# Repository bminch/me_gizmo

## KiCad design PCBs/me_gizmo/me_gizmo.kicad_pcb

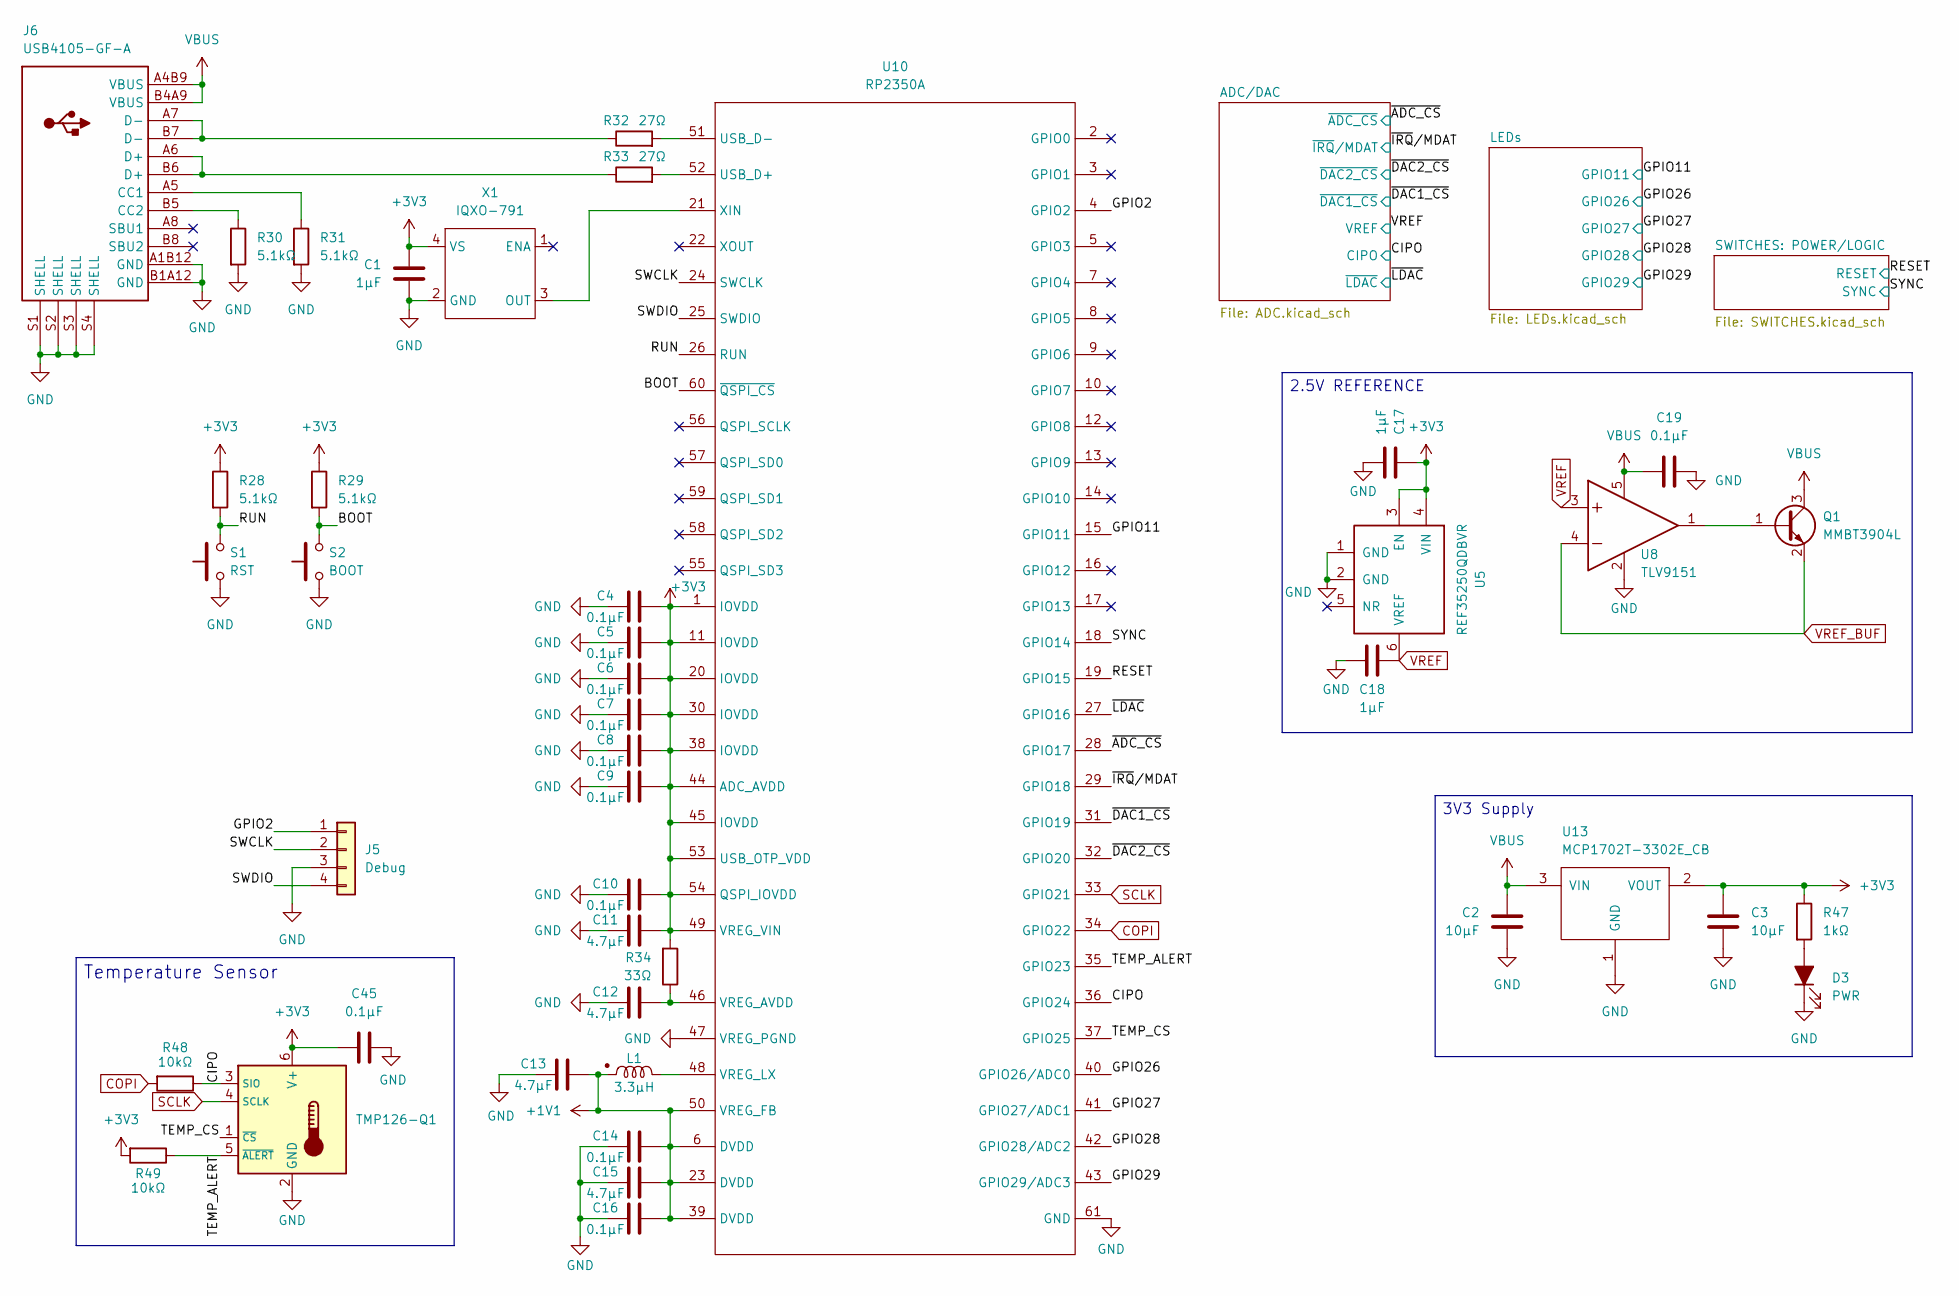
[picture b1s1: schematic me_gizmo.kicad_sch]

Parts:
C1: 1µF; C_0402_1005Metric
C2, C3: 10µF; C_0603_1608Metric
C4, C5, C6, C7, C8, C9, C10, C14, C16: 0.1µF; C_0402_1005Metric
C11, C12, C13, C15: 4.7µF; C_0402_1005Metric
C17, C18: 1µF; C_0603_1608Metric
C19, C45: 0.1µF; C_0603_1608Metric
D3: PWR; LED_0805_2012Metric
J5: Debug; PinHeader_1x04_P2.54mm_Vertical
J6: USB4105-GF-A
L1: 3.3µH; AOTA-B201610S3R3-101-T
Q1: MMBT3904L; SOT-23
R28, R29, R30, R31: 5.1kΩ; R_0603_1608Metric
R32, R33: 27Ω; R_0402_1005Metric
R34: 33Ω; R_0402_1005Metric
R47: 1kΩ; R_0603_1608Metric
R48, R49: 10kΩ; R_0603_1608Metric
S1: RST; SW_SPST_B3U-1000P
S2: BOOT; SW_SPST_B3U-1000P
U5: REF35250QDBVR; SOT-23-6
U6: TMP126-Q1; SOT-23-6
U8: TLV9151; SOT-23-5
U10: RP2350A; RP2350A_QFN-60_EP_7.75x7.75_Pitch0.4mm
U13: MCP1702T-3302E_CB; SOT-23
X1: IQXO-791

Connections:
+1V1: C13.2, C14.2, C15.2, C16.2, L1.1, U10.6 (DVDD), U10.23 (DVDD), U10.39 (DVDD), U10.50 (VREG_FB)
+3V3: C1.2, C3.1, C4.2, C5.2, C6.2, C7.2, C8.2, C9.2, C10.2, C11.2, C17.1, C45.1, R28.1, R29.1, R34.2, R47.1, R49.2, U5.3 (EN), U5.4 (VIN), U6.6 (V+), U10.1 (IOVDD), U10.11 (IOVDD), U10.20 (IOVDD), U10.30 (IOVDD), U10.38 (IOVDD), U10.44 (ADC_AVDD), U10.45 (IOVDD), U10.49 (VREG_VIN), U10.53 (USB_OTP_VDD), U10.54 (QSPI_IOVDD), U13.2 (VOUT), X1.4 (VS); also elsewhere on the board
/BOOT: R29.2, S2.2, U10.60 (~QSPI_CS)
/CIPO: R48.1, U6.3 (SIO), U10.36 (GPIO24); also elsewhere on the board
/GPIO2: J5.1, U10.4 (GPIO2)
/GPIO11: U10.15 (GPIO11); also elsewhere on the board
/GPIO26: U10.40 (GPIO26/ADC0); also elsewhere on the board
/GPIO27: U10.41 (GPIO27/ADC1); also elsewhere on the board
/GPIO28: U10.42 (GPIO28/ADC2); also elsewhere on the board
/GPIO29: U10.43 (GPIO29/ADC3); also elsewhere on the board
/RESET: U10.19 (GPIO15); also elsewhere on the board
/RUN: R28.2, S1.2, U10.26 (RUN)
/SWCLK: J5.2, U10.24 (SWCLK)
/SWDIO: J5.4, U10.25 (SWDIO)
/SYNC: U10.18 (GPIO14); also elsewhere on the board
/TEMP_ALERT: R49.1, U6.5 (~ALERT), U10.35 (GPIO23)
/TEMP_CS: U6.1 (~CS), U10.37 (GPIO25)
/~ADC_CS: U10.28 (GPIO17); also elsewhere on the board
/~DAC1_CS: U10.31 (GPIO19); also elsewhere on the board
/~DAC2_CS: U10.32 (GPIO20); also elsewhere on the board
/~IRQ/MDAT: U10.29 (GPIO18); also elsewhere on the board
/~LDAC: U10.27 (GPIO16); also elsewhere on the board
COPI: R48.2, U10.34 (GPIO22); also elsewhere on the board
GND: C1.1, C2.1, C3.2, C4.1, C5.1, C6.1, C7.1, C8.1, C9.1, C10.1, C11.1, C12.1, C13.1, C14.1, C15.1, C16.1, C17.2, C18.2, C19.2, C45.2, D3.1 (K), J5.3, J6.A1B12 (GND), J6.B1A12 (GND), J6.S1 (SHELL), J6.S2 (SHELL), J6.S3 (SHELL), J6.S4 (SHELL), R30.2, R31.2, S1.1, S2.1, U5.1 (GND), U5.2 (GND), U6.2 (GND), U8.2, U10.47 (VREG_PGND), U10.61 (GND), U13.1 (GND), X1.2 (GND); also elsewhere on the board
unnamed: D3.2 (A), R47.2
unnamed: J6.A5 (CC1), R31.1
unnamed: J6.B5 (CC2), R30.1
unnamed: J6.A6 (D+), J6.B6 (D+), R33.1
unnamed: J6.A7 (D-), J6.B7 (D-), R32.1
unnamed: Q1.1 (B), U8.1
unnamed: R33.2, U10.52 (USB_D+)
unnamed: R32.2, U10.51 (USB_D-)
unnamed: C12.2, R34.1, U10.46 (VREG_AVDD)
unnamed: L1.2, U10.48 (VREG_LX)
unnamed: U10.21 (XIN), X1.3 (OUT)
SCLK: U6.4 (SCLK), U10.33 (GPIO21); also elsewhere on the board
VBUS: C2.2, C19.1, J6.A4B9 (VBUS), J6.B4A9 (VBUS), Q1.3 (C), U8.5, U13.3 (VIN)
VREF: C18.1, U5.6 (VREF), U8.3; also elsewhere on the board
VREF_BUF: Q1.2 (E), U8.4; also elsewhere on the board

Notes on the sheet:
2.5V REFERENCE
Temperature Sensor
3V3 Supply

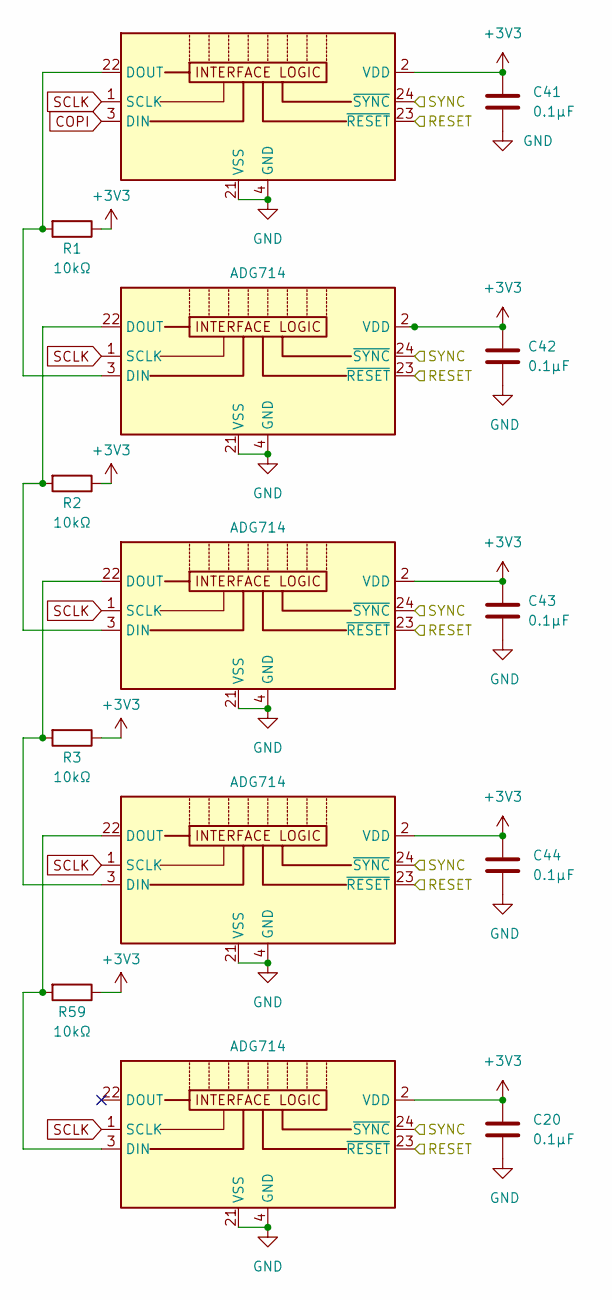
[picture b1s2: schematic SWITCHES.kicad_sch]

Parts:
C20, C41, C42, C43, C44: 0.1µF; C_0603_1608Metric
R1, R2, R3, R59: 10kΩ; R_0603_1608Metric
U1, U2, U3, U4, U7: ADG714; TSSOP-24_4.4x7.8mm_P0.65mm

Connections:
+3V3: C20.1, C41.1, C42.1, C43.1, C44.1, R1.1, R2.1, R3.1, R59.1, U1.2 (VDD), U2.2 (VDD), U3.2 (VDD), U4.2 (VDD), U7.2 (VDD); also elsewhere on the board
/RESET: U1.23 (~RESET), U2.23 (~RESET), U3.23 (~RESET), U4.23 (~RESET), U7.23 (~RESET); also elsewhere on the board
/SYNC: U1.24 (~SYNC), U2.24 (~SYNC), U3.24 (~SYNC), U4.24 (~SYNC), U7.24 (~SYNC); also elsewhere on the board
COPI: U7.3 (DIN); also elsewhere on the board
GND: C20.2, C41.2, C42.2, C43.2, C44.2, U1.4 (GND), U1.21 (VSS), U2.4 (GND), U2.21 (VSS), U3.4 (GND), U3.21 (VSS), U4.4 (GND), U4.21 (VSS), U7.4 (GND), U7.21 (VSS); also elsewhere on the board
unnamed: R1.2, U1.3 (DIN), U7.22 (DOUT)
unnamed: R2.2, U1.22 (DOUT), U4.3 (DIN)
unnamed: R59.2, U2.3 (DIN), U3.22 (DOUT)
unnamed: R3.2, U3.3 (DIN), U4.22 (DOUT)
SCLK: U1.1 (SCLK), U2.1 (SCLK), U3.1 (SCLK), U4.1 (SCLK), U7.1 (SCLK); also elsewhere on the board

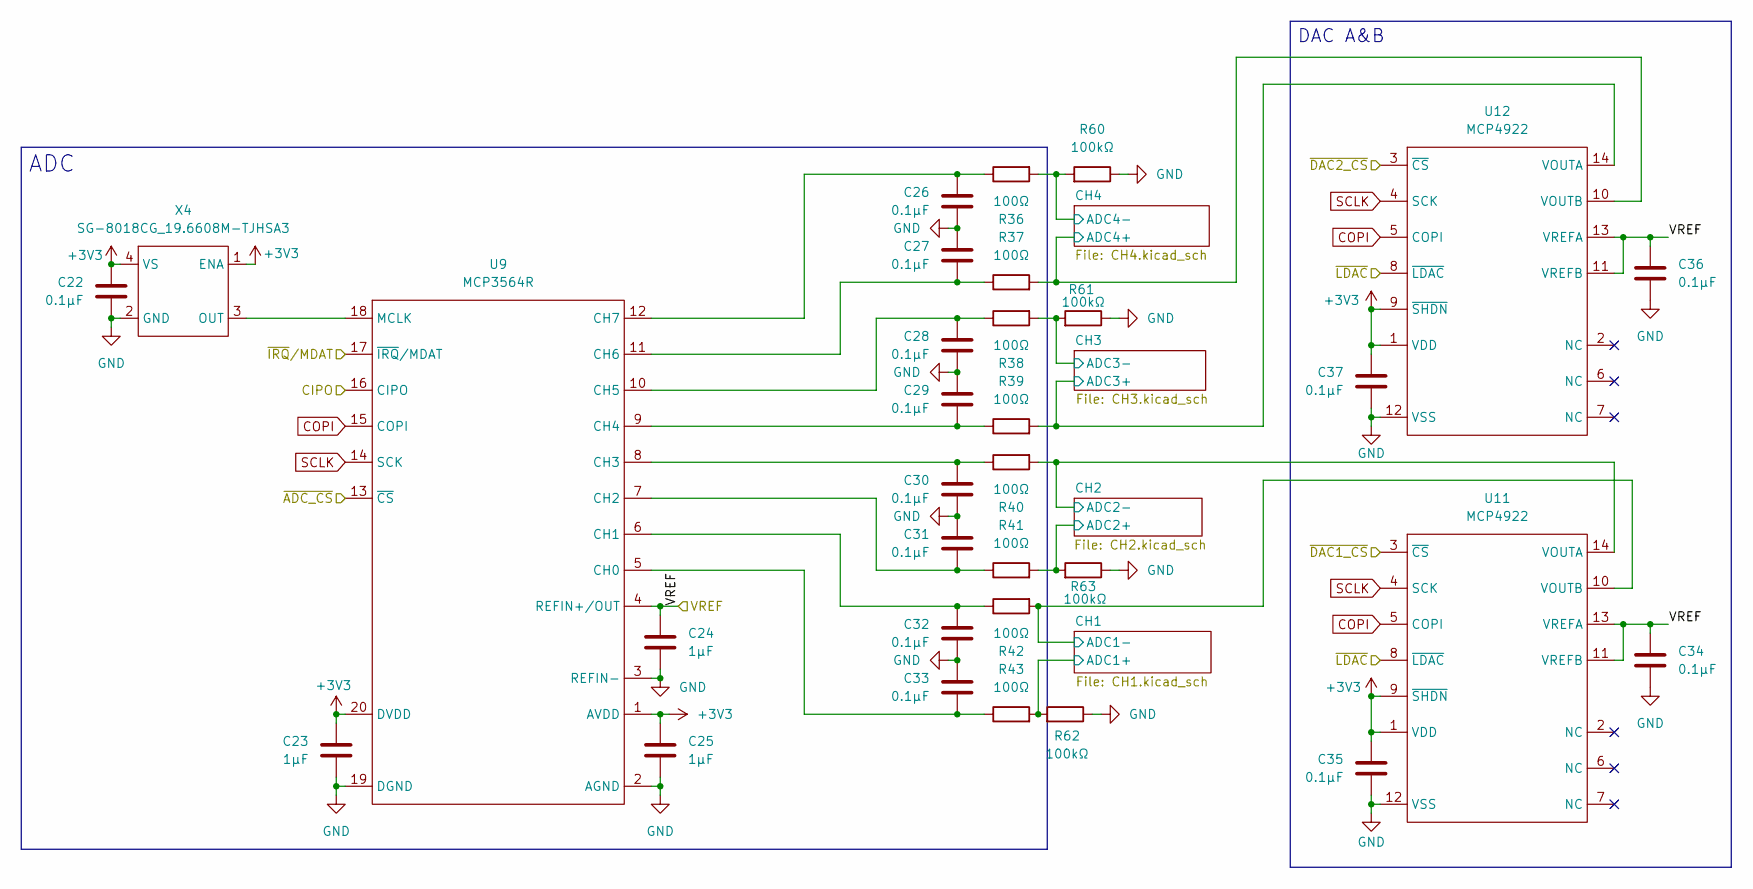
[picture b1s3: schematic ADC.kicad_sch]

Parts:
C22, C26, C27, C28, C29, C30, C31, C32, C33, C34, C35, C36, C37: 0.1µF; C_0603_1608Metric
C23, C24, C25: 1µF; C_0603_1608Metric
R36, R37, R38, R39, R40, R41, R42, R43: 100Ω; R_0603_1608Metric
R60, R61, R62, R63: 100kΩ; R_0603_1608Metric
U9: MCP3564R; TSSOP-20_4.4x6.5mm_P0.65mm
U11, U12: MCP4922; TSSOP-14_4.4x5mm_P0.65mm
X4: SG-8018CG_19.6608M-TJHSA3; Crystal_SMD_2520-4Pin_2.5x2.0mm

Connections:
+3V3: C22.1, C23.1, C25.1, C35.1, C37.1, U9.1 (AVDD), U9.20 (DVDD), U11.1 (VDD), U11.9 (~SHDN), U12.1 (VDD), U12.9 (~SHDN), X4.1 (ENA), X4.4 (VS); also elsewhere on the board
/ADC/DAC/CH1/ADC1+: R43.2, R62.2; also elsewhere on the board
/ADC/DAC/CH1/ADC1-: R42.2, U11.10 (VOUTB); also elsewhere on the board
/ADC/DAC/CH2/ADC2+: R41.2, R63.2; also elsewhere on the board
/ADC/DAC/CH2/ADC2-: R40.2, U11.14 (VOUTA); also elsewhere on the board
/ADC/DAC/CH3/ADC3+: R39.2, U12.14 (VOUTA); also elsewhere on the board
/ADC/DAC/CH3/ADC3-: R38.2, R61.2; also elsewhere on the board
/ADC/DAC/CH4/ADC4+: R37.2, U12.10 (VOUTB); also elsewhere on the board
/ADC/DAC/CH4/ADC4-: R36.2, R60.2; also elsewhere on the board
/CIPO: U9.16 (CIPO); also elsewhere on the board
/~ADC_CS: U9.13 (~CS); also elsewhere on the board
/~DAC1_CS: U11.3 (~CS); also elsewhere on the board
/~DAC2_CS: U12.3 (~CS); also elsewhere on the board
/~IRQ/MDAT: U9.17 (~IRQ/MDAT); also elsewhere on the board
/~LDAC: U11.8 (~LDAC), U12.8 (~LDAC); also elsewhere on the board
COPI: U9.15 (COPI), U11.5 (COPI), U12.5 (COPI); also elsewhere on the board
GND: C22.2, C23.2, C24.2, C25.2, C26.2, C27.1, C28.2, C29.1, C30.2, C31.1, C32.2, C33.1, C34.2, C35.2, C36.2, C37.2, R60.1, R61.1, R62.1, R63.1, U9.2 (AGND), U9.3 (REFIN-), U9.19 (DGND), U11.12 (VSS), U12.12 (VSS), X4.2 (GND); also elsewhere on the board
unnamed: C33.2, R43.1, U9.5 (CH0)
unnamed: C32.1, R42.1, U9.6 (CH1)
unnamed: C31.2, R41.1, U9.7 (CH2)
unnamed: C30.1, R40.1, U9.8 (CH3)
unnamed: C29.2, R39.1, U9.9 (CH4)
unnamed: C28.1, R38.1, U9.10 (CH5)
unnamed: C27.2, R37.1, U9.11 (CH6)
unnamed: C26.1, R36.1, U9.12 (CH7)
unnamed: U9.18 (MCLK), X4.3 (OUT)
SCLK: U9.14 (SCK), U11.4 (SCK), U12.4 (SCK); also elsewhere on the board
VREF: C24.1, C34.1, C36.1, U9.4 (REFIN+/OUT), U11.11 (VREFB), U11.13 (VREFA), U12.11 (VREFB), U12.13 (VREFA); also elsewhere on the board

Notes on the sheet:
DAC A&B
ADC

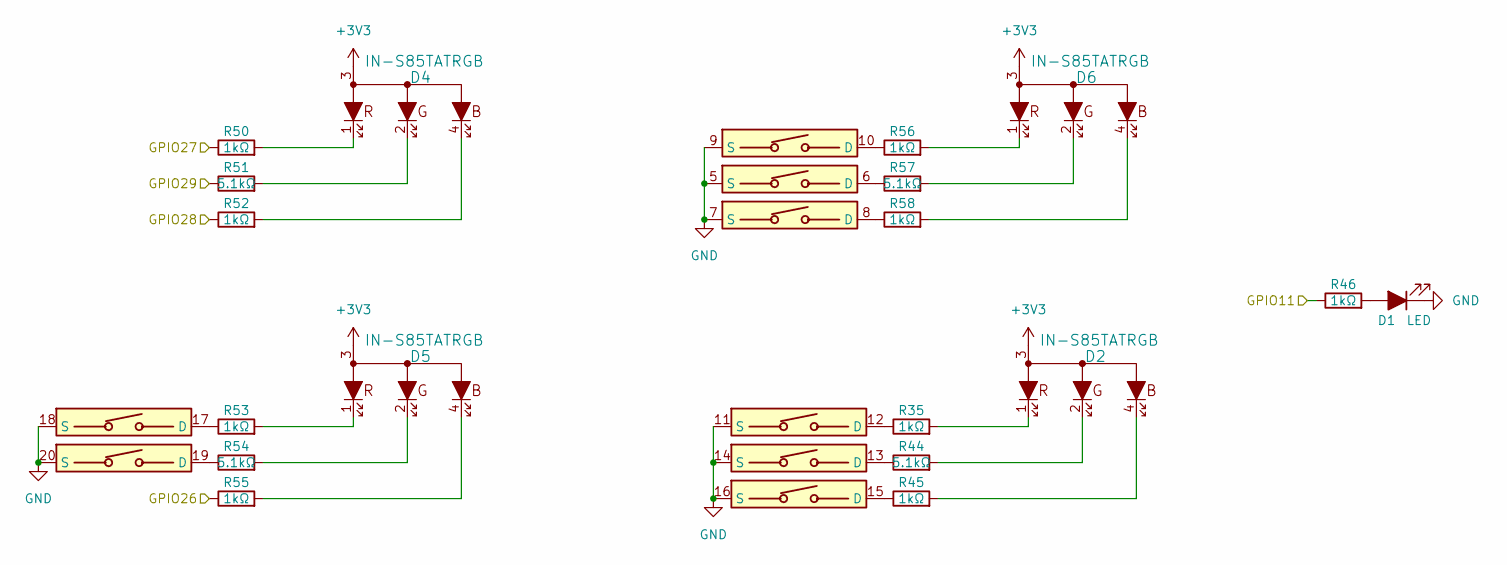
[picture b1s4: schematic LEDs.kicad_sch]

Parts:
D1: LED; LED_0805_2012Metric
D2, D4, D5, D6: IN-S85TATRGB
R35, R45, R46, R50, R52, R53, R55, R56, R58: 1kΩ; R_0603_1608Metric
R44, R51, R54, R57: 5.1kΩ; R_0603_1608Metric
U7: ADG714; TSSOP-24_4.4x7.8mm_P0.65mm

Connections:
+3V3: D2.3, D4.3, D5.3, D6.3; also elsewhere on the board
/GPIO11: R46.1; also elsewhere on the board
/GPIO26: R55.1; also elsewhere on the board
/GPIO27: R50.1; also elsewhere on the board
/GPIO28: R52.1; also elsewhere on the board
/GPIO29: R51.1; also elsewhere on the board
GND: D1.1 (K), U7.5 (S), U7.7 (S), U7.9 (S), U7.11 (S), U7.14 (S), U7.16 (S), U7.18 (S), U7.20 (S); also elsewhere on the board
unnamed: D1.2 (A), R46.2
unnamed: D2.1, R35.2
unnamed: D2.2, R44.2
unnamed: D2.4, R45.2
unnamed: D4.1, R50.2
unnamed: D4.2, R51.2
unnamed: D4.4, R52.2
unnamed: D5.1, R53.2
unnamed: D5.2, R54.2
unnamed: D5.4, R55.2
unnamed: D6.1, R56.2
unnamed: D6.2, R57.2
unnamed: D6.4, R58.2
unnamed: R57.1, U7.6 (D)
unnamed: R58.1, U7.8 (D)
unnamed: R56.1, U7.10 (D)
unnamed: R35.1, U7.12 (D)
unnamed: R44.1, U7.13 (D)
unnamed: R45.1, U7.15 (D)
unnamed: R53.1, U7.17 (D)
unnamed: R54.1, U7.19 (D)

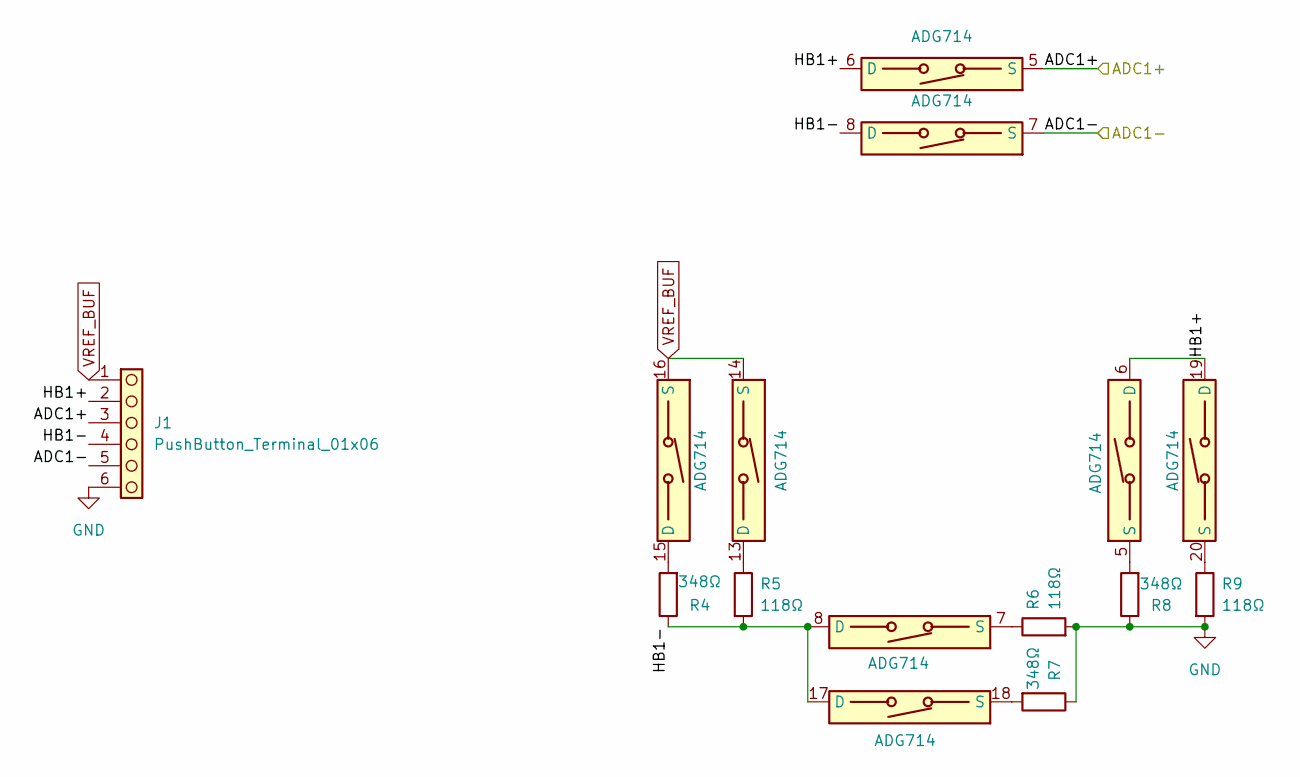
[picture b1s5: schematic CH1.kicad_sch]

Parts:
J1: PushButton_Terminal_01x06; TerminalBlock_WAGO_233-506_2x06_P2.54mm
R4, R7, R8: 348Ω; R_0603_1608Metric
R5, R6, R9: 118Ω; R_0603_1608Metric
U1, U2, U3: ADG714; TSSOP-24_4.4x7.8mm_P0.65mm

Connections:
/ADC/DAC/CH1/ADC1+: J1.3, U3.5 (S); also elsewhere on the board
/ADC/DAC/CH1/ADC1-: J1.5, U3.7 (S); also elsewhere on the board
/ADC/DAC/CH1/HB1+: J1.2, U2.6 (D), U2.19 (D), U3.6 (D)
/ADC/DAC/CH1/HB1-: J1.4, R4.1, R5.2, U2.8 (D), U2.17 (D), U3.8 (D)
GND: J1.6, R6.2, R7.1, R8.1, R9.2; also elsewhere on the board
unnamed: R5.1, U1.13 (D)
unnamed: R4.2, U1.15 (D)
unnamed: R8.2, U2.5 (S)
unnamed: R6.1, U2.7 (S)
unnamed: R7.2, U2.18 (S)
unnamed: R9.1, U2.20 (S)
VREF_BUF: J1.1, U1.14 (S), U1.16 (S); also elsewhere on the board

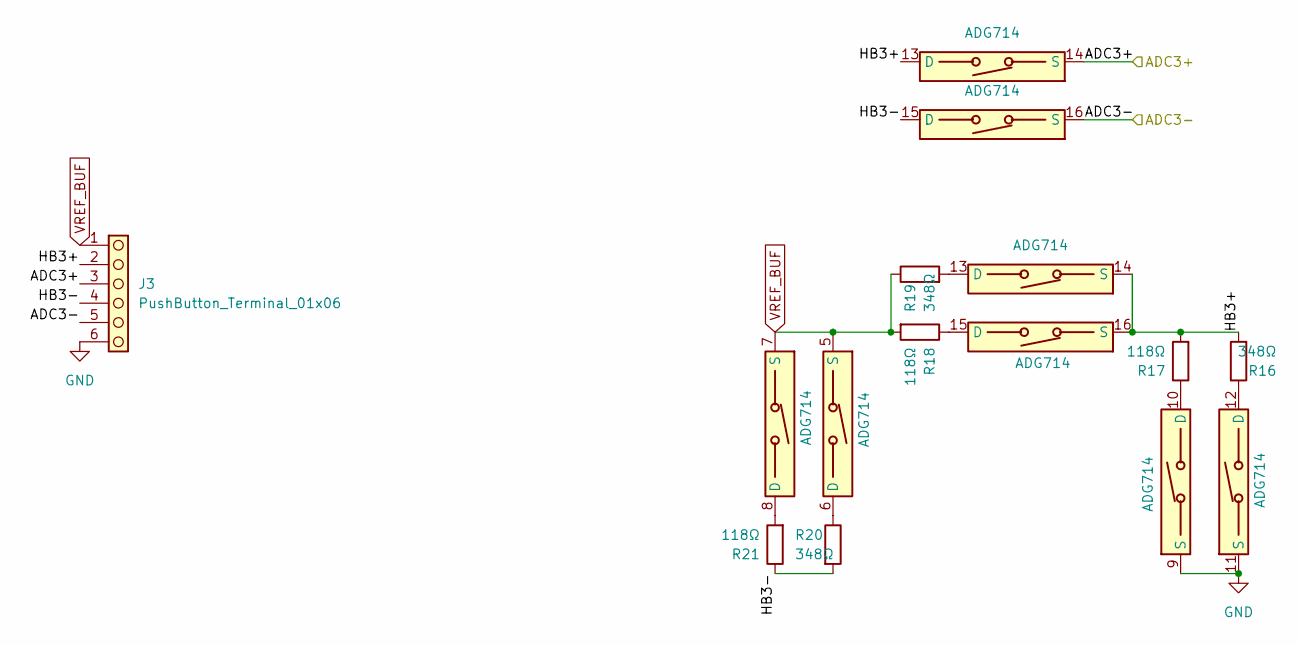
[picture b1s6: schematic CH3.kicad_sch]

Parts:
J3: PushButton_Terminal_01x06; TerminalBlock_WAGO_233-506_2x06_P2.54mm
R16, R19, R20: 348Ω; R_0603_1608Metric
R17, R18, R21: 118Ω; R_0603_1608Metric
U1, U3, U4: ADG714; TSSOP-24_4.4x7.8mm_P0.65mm

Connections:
/ADC/DAC/CH3/ADC3+: J3.3, U3.14 (S); also elsewhere on the board
/ADC/DAC/CH3/ADC3-: J3.5, U3.16 (S); also elsewhere on the board
/ADC/DAC/CH3/HB3+: J3.2, R16.2, R17.2, U3.13 (D), U4.14 (S), U4.16 (S)
/ADC/DAC/CH3/HB3-: J3.4, R20.2, R21.1, U3.15 (D)
GND: J3.6, U4.9 (S), U4.11 (S); also elsewhere on the board
unnamed: R20.1, U1.6 (D)
unnamed: R21.2, U1.8 (D)
unnamed: R17.1, U4.10 (D)
unnamed: R16.1, U4.12 (D)
unnamed: R19.2, U4.13 (D)
unnamed: R18.1, U4.15 (D)
VREF_BUF: J3.1, R18.2, R19.1, U1.5 (S), U1.7 (S); also elsewhere on the board

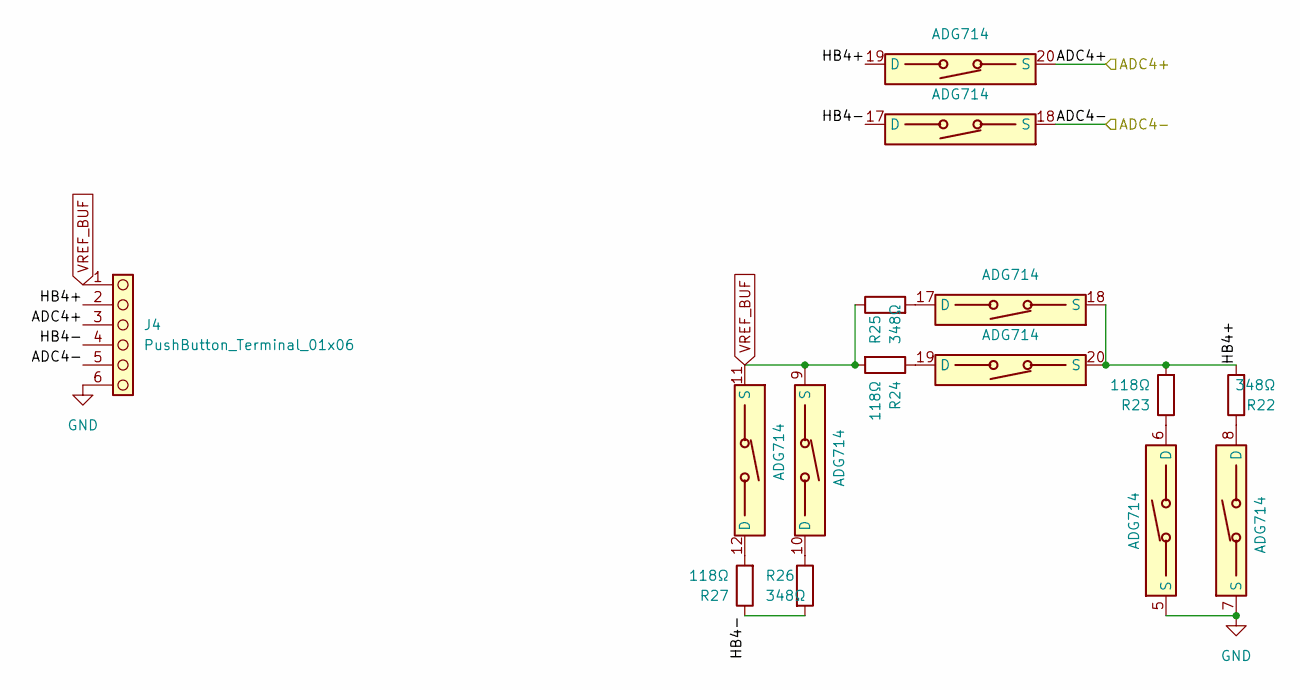
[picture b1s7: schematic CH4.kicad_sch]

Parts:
J4: PushButton_Terminal_01x06; TerminalBlock_WAGO_233-506_2x06_P2.54mm
R22, R25, R26: 348Ω; R_0603_1608Metric
R23, R24, R27: 118Ω; R_0603_1608Metric
U1, U3, U4: ADG714; TSSOP-24_4.4x7.8mm_P0.65mm

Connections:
/ADC/DAC/CH4/ADC4+: J4.3, U3.20 (S); also elsewhere on the board
/ADC/DAC/CH4/ADC4-: J4.5, U3.18 (S); also elsewhere on the board
/ADC/DAC/CH4/HB4+: J4.2, R22.2, R23.2, U3.19 (D), U4.18 (S), U4.20 (S)
/ADC/DAC/CH4/HB4-: J4.4, R26.2, R27.1, U3.17 (D)
GND: J4.6, U4.5 (S), U4.7 (S); also elsewhere on the board
unnamed: R26.1, U1.10 (D)
unnamed: R27.2, U1.12 (D)
unnamed: R23.1, U4.6 (D)
unnamed: R22.1, U4.8 (D)
unnamed: R25.2, U4.17 (D)
unnamed: R24.1, U4.19 (D)
VREF_BUF: J4.1, R24.2, R25.1, U1.9 (S), U1.11 (S); also elsewhere on the board

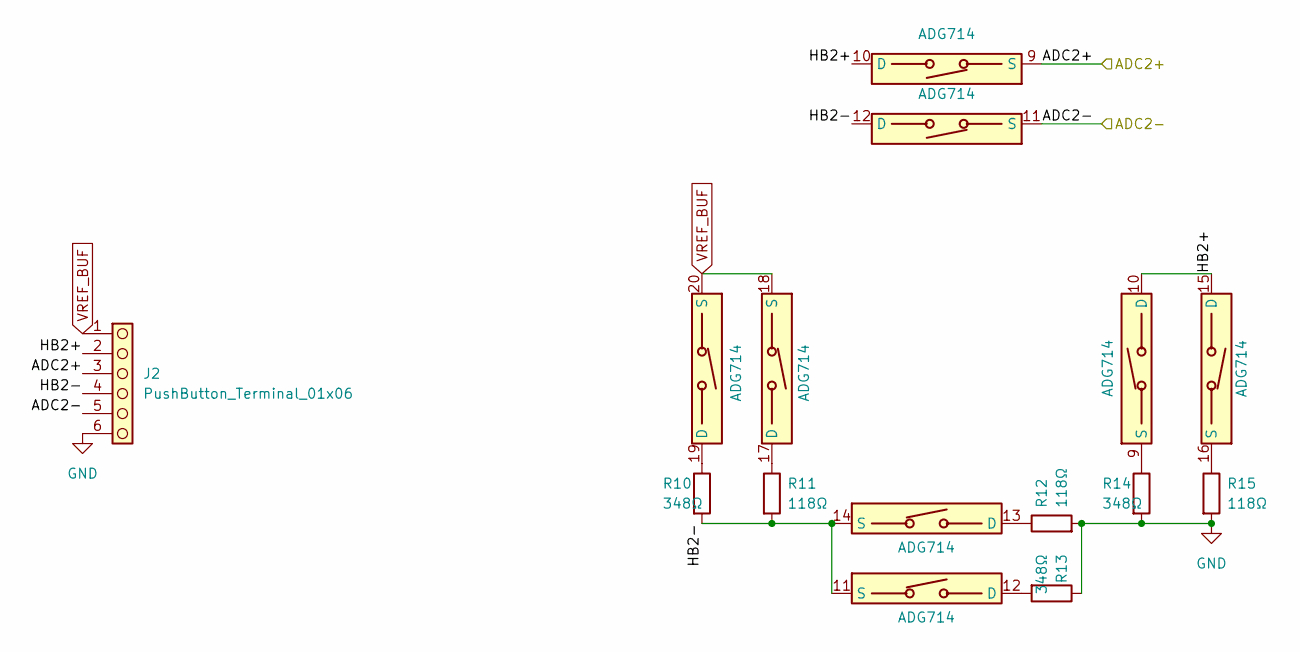
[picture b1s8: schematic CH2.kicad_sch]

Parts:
J2: PushButton_Terminal_01x06; TerminalBlock_WAGO_233-506_2x06_P2.54mm
R10, R13, R14: 348Ω; R_0603_1608Metric
R11, R12, R15: 118Ω; R_0603_1608Metric
U1, U2, U3: ADG714; TSSOP-24_4.4x7.8mm_P0.65mm

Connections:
/ADC/DAC/CH2/ADC2+: J2.3, U3.9 (S); also elsewhere on the board
/ADC/DAC/CH2/ADC2-: J2.5, U3.11 (S); also elsewhere on the board
/ADC/DAC/CH2/HB2+: J2.2, U2.10 (D), U2.15 (D), U3.10 (D)
/ADC/DAC/CH2/HB2-: J2.4, R10.2, R11.2, U2.11 (S), U2.14 (S), U3.12 (D)
GND: J2.6, R12.2, R13.1, R14.2, R15.2; also elsewhere on the board
unnamed: R11.1, U1.17 (D)
unnamed: R10.1, U1.19 (D)
unnamed: R14.1, U2.9 (S)
unnamed: R13.2, U2.12 (D)
unnamed: R12.1, U2.13 (D)
unnamed: R15.1, U2.16 (S)
VREF_BUF: J2.1, U1.18 (S), U1.20 (S); also elsewhere on the board

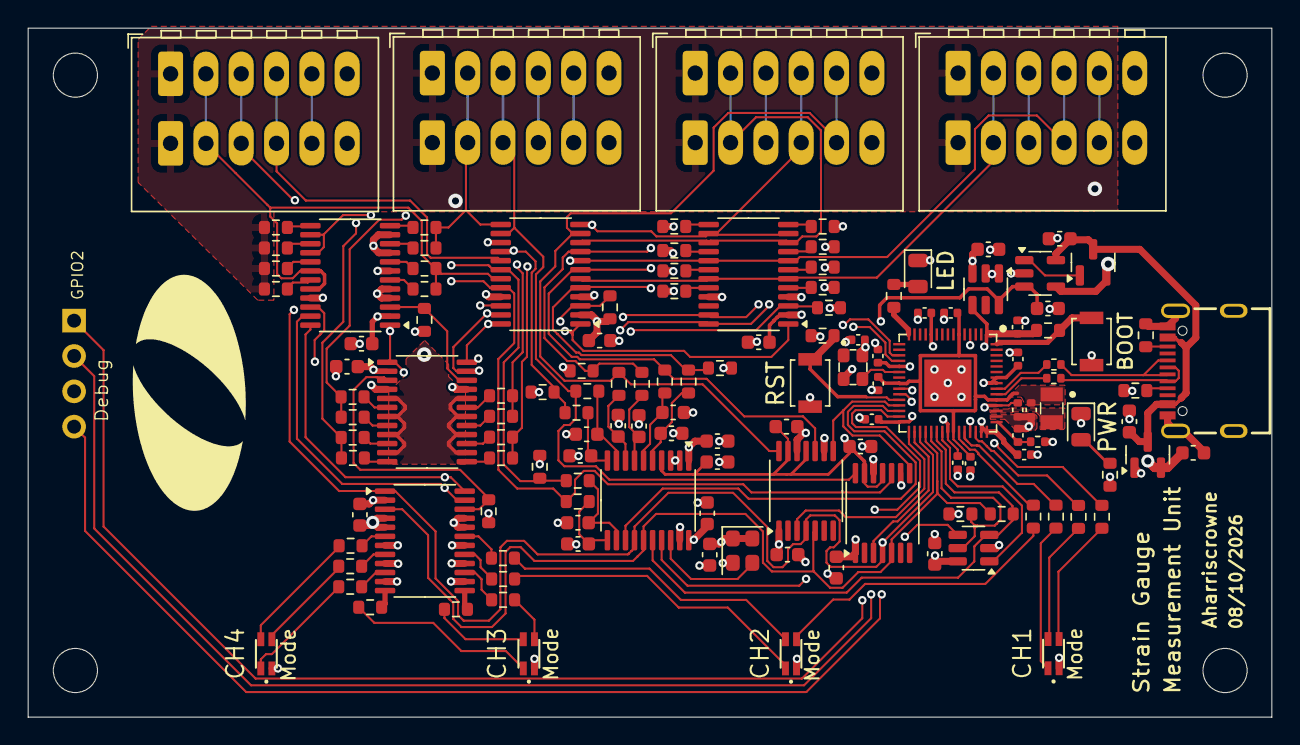
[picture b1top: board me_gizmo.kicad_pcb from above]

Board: 4 copper layers, 89.4 x 49.5 mm, 136 parts (0 on the bottom side), 113 nets.

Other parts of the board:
svg2mod: G***; OlinLogo_0.3in

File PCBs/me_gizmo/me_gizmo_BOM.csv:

Id,Designator,Footprint,Quantity,Designation
1,"C24,C25,C17,C23,C18",C_0603_1608Metric,5,1µF
2,"J4,J1,J2,J3",TerminalBlock_WAGO_233-506_2x06_P2.54mm,4,PushButton_Terminal_01x06
3,"C34,C22,C33,C35,C37,C29,C42,C28,C31,C30,C43,C26,C27,C36,C19,C32,C45,C20,C41,C44",C_0603_1608Metric,20,0.1µF
4,"R1-R3, R48, R49, R59",R_0603_1608Metric,6,10kΩ
5,"R32,R33",R_0402_1005Metric,2,27Ω
6,"R23,R27,R9,R21,R5,R11,R12,R17,R18,R6,R15,R24",R_0603_1608Metric,12,118Ω
7,"C2,C3",C_0603_1608Metric,2,10µF
8,"R56,R45,R52,R35,R46,R53,R47,R58,R50,R55",R_0603_1608Metric,10,1kΩ
9,D3,LED_0805_2012Metric,1,PWR
10,"R4,R26,R16,R7,R25,R20,R22,R14,R19,R13,R10,R8",R_0603_1608Metric,12,348Ω
11,"C12,C15",C_0402_1005Metric,2,4.7µF
12,"R42,R41,R36,R40,R37,R38,R39,R43",R_0603_1608Metric,8,100Ω
13,S1,SW_SPST_B3U-1000P,1,RST
14,D1,LED_0805_2012Metric,1,LED
15,"U3,U4,U2,U1,U7",TSSOP-24_4.4x7.8mm_P0.65mm,5,ADG714
16,"C16,C10,C8,C5,C9,C14,C6,C7,C4, C1",C_0402_1005Metric,9,0.1µF
17,X4,Crystal_SMD_2520-4Pin_2.5x2.0mm,1,SG-8018CG_19.6608M-TJHSA3
18,U5,SOT-23-6,1,REF35250QDBVR
19,U8,SOT-23-5,1,TLV9151
20,"D6,D4,D5,D2",IN-S85TATRGB,4,IN-S85TATRGB
21,"U12,U11",TSSOP-14_4.4x5mm_P0.65mm,2,MCP4922
22,Q1,SOT-23,1,MMBT3904L
23,"R28-R31,R44,R51,R54, R57",R_0603_1608Metric,8,5.1kΩ
24,U10,RP2354A_QFN-60_EP_7.75x7.75_Pitch0.4mm,1,RP2354A
25,R34,R_0402_1005Metric,1,33Ω
26,U13,SOT-23,1,MCP1702T-3302E_CB
27,U6,SOT-23-6,1,TMP126-Q1
28,S2,SW_SPST_B3U-1000P,1,BOOT
29,"C13,C11",C_0402_1005Metric,2,4.7µF
30,L1,AOTA-B201610S3R3-101-T,1,3.3µH
31,X1,IQXO-791,1,IQXO-791
32,U9,TSSOP-20_4.4x6.5mm_P0.65mm,1,MCP3564R
33,J6,USB4105-GF-A,1,USB4105-GF-A
34,C1,C_0402_1005Metric,1,1µF

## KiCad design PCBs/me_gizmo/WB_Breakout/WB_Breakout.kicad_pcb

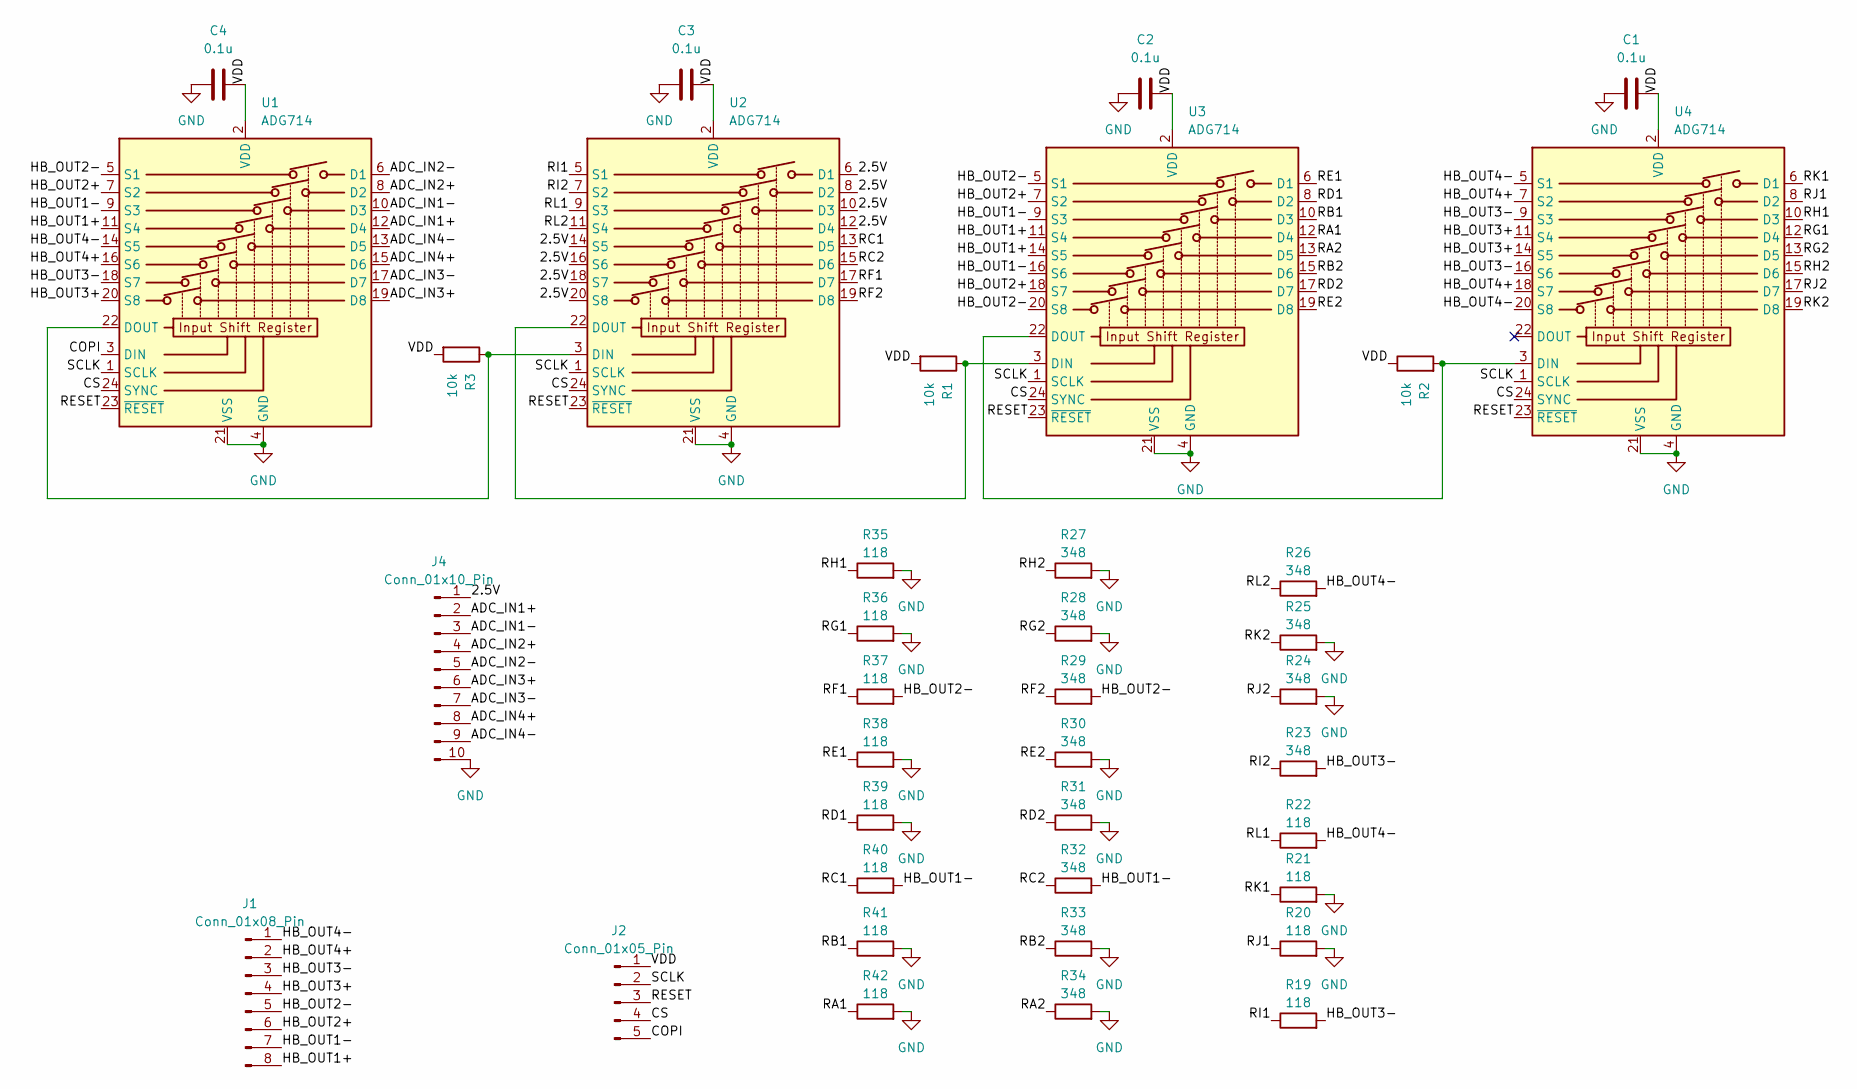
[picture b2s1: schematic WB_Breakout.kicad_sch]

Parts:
C1, C2, C3, C4: 0.1u; C_0603_1608Metric
J1: Conn_01x08_Pin; PinHeader_1x08_P2.54mm_Vertical
J2: Conn_01x05_Pin; PinHeader_1x05_P2.54mm_Vertical
J4: Conn_01x10_Pin; PinHeader_1x10_P2.54mm_Vertical
R1, R2, R3: 10k; R_0603_1608Metric
R19, R20, R21, R22, R35, R36, R37, R38, R39, R40, R41, R42: 118; R_0603_1608Metric
R23, R24, R25, R26, R27, R28, R29, R30, R31, R32, R33, R34: 348; R_0603_1608Metric
U1, U2, U3, U4: ADG714; TSSOP-24_4.4x7.8mm_P0.65mm

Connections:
/2.5V: J4.1, U2.6 (D1), U2.8 (D2), U2.10 (D3), U2.12 (D4), U2.14 (S5), U2.16 (S6), U2.18 (S7), U2.20 (S8)
/ADC_IN1+: J4.2, U1.12 (D4)
/ADC_IN1-: J4.3, U1.10 (D3)
/ADC_IN2+: J4.4, U1.8 (D2)
/ADC_IN2-: J4.5, U1.6 (D1)
/ADC_IN3+: J4.6, U1.19 (D8)
/ADC_IN3-: J4.7, U1.17 (D7)
/ADC_IN4+: J4.8, U1.15 (D6)
/ADC_IN4-: J4.9, U1.13 (D5)
/COPI: J2.5, U1.3 (DIN)
/CS: J2.4, U1.24 (SYNC), U2.24 (SYNC), U3.24 (SYNC), U4.24 (SYNC)
/HB_OUT1+: J1.8, U1.11 (S4), U3.11 (S4), U3.14 (S5)
/HB_OUT1-: J1.7, R32.2, R40.2, U1.9 (S3), U3.9 (S3), U3.16 (S6)
/HB_OUT2+: J1.6, U1.7 (S2), U3.7 (S2), U3.18 (S7)
/HB_OUT2-: J1.5, R29.2, R37.2, U1.5 (S1), U3.5 (S1), U3.20 (S8)
/HB_OUT3+: J1.4, U1.20 (S8), U4.11 (S4), U4.14 (S5)
/HB_OUT3-: J1.3, R19.2, R23.2, U1.18 (S7), U4.9 (S3), U4.16 (S6)
/HB_OUT4+: J1.2, U1.16 (S6), U4.7 (S2), U4.18 (S7)
/HB_OUT4-: J1.1, R22.2, R26.2, U1.14 (S5), U4.5 (S1), U4.20 (S8)
/RA1: R42.1, U3.12 (D4)
/RA2: R34.1, U3.13 (D5)
/RB1: R41.1, U3.10 (D3)
/RB2: R33.1, U3.15 (D6)
/RC1: R40.1, U2.13 (D5)
/RC2: R32.1, U2.15 (D6)
/RD1: R39.1, U3.8 (D2)
/RD2: R31.1, U3.17 (D7)
/RE1: R38.1, U3.6 (D1)
/RE2: R30.1, U3.19 (D8)
/RESET: J2.3, U1.23 (~RESET), U2.23 (~RESET), U3.23 (~RESET), U4.23 (~RESET)
/RF1: R37.1, U2.17 (D7)
/RF2: R29.1, U2.19 (D8)
/RG1: R36.1, U4.12 (D4)
/RG2: R28.1, U4.13 (D5)
/RH1: R35.1, U4.10 (D3)
/RH2: R27.1, U4.15 (D6)
/RI1: R19.1, U2.5 (S1)
/RI2: R23.1, U2.7 (S2)
/RJ1: R20.1, U4.8 (D2)
/RJ2: R24.1, U4.17 (D7)
/RK1: R21.1, U4.6 (D1)
/RK2: R25.1, U4.19 (D8)
/RL1: R22.1, U2.9 (S3)
/RL2: R26.1, U2.11 (S4)
/SCLK: J2.2, U1.1 (SCLK), U2.1 (SCLK), U3.1 (SCLK), U4.1 (SCLK)
/VDD: C1.2, C2.2, C3.2, C4.2, J2.1, R1.2, R2.1, R3.2, U1.2 (VDD), U2.2 (VDD), U3.2 (VDD), U4.2 (VDD)
GND: C1.1, C2.1, C3.1, C4.1, J4.10, R20.2, R21.2, R24.2, R25.2, R27.2, R28.2, R30.2, R31.2, R33.2, R34.2, R35.2, R36.2, R38.2, R39.2, R41.2, R42.2, U1.4 (GND), U1.21 (VSS), U2.4 (GND), U2.21 (VSS), U3.4 (GND), U3.21 (VSS), U4.4 (GND), U4.21 (VSS)
unnamed: R3.1, U1.22 (DOUT), U2.3 (DIN)
unnamed: R1.1, U2.22 (DOUT), U3.3 (DIN)
unnamed: R2.2, U3.22 (DOUT), U4.3 (DIN)

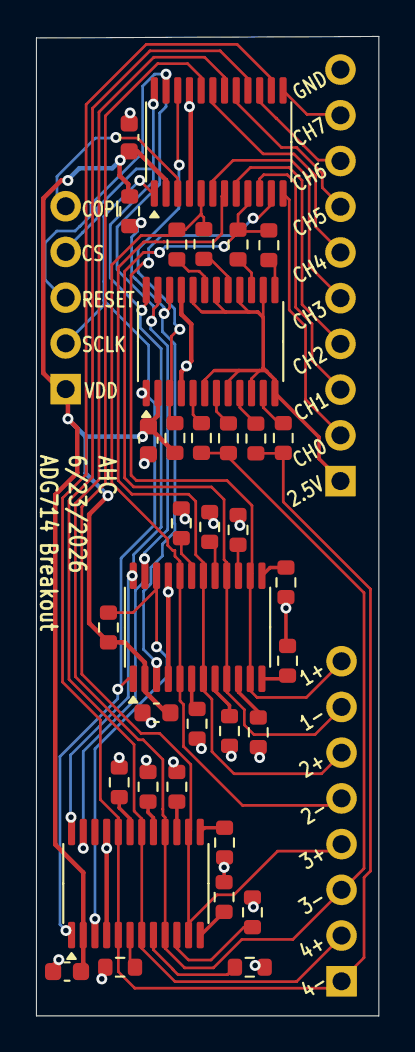
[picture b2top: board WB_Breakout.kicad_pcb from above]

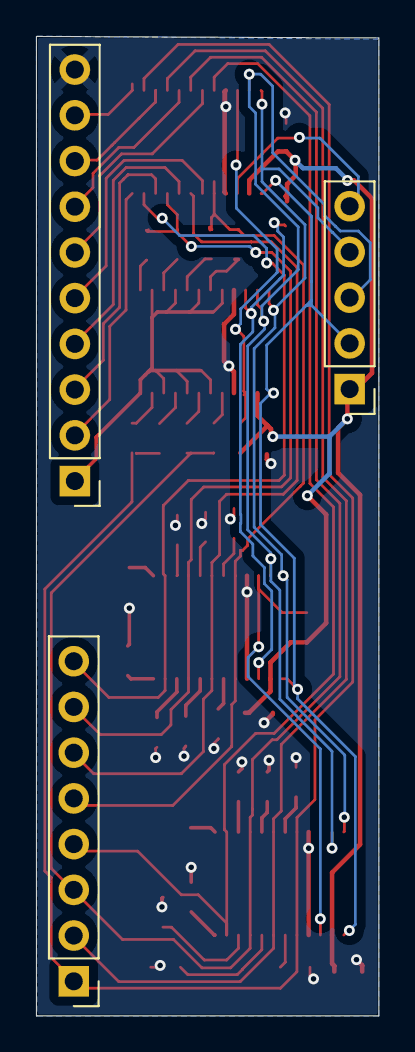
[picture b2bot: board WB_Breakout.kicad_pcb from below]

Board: 2 copper layers, 19.0 x 54.4 mm, 38 parts (3 on the bottom side), 50 nets.
